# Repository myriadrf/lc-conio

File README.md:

# LibreCellular Remote Console and Power/Reset Control Boards

The CONIO boards provide remote console and power/reset control for SDR base
stations in the [LibreCellular CI hardware platform][1]. 

* **CONIO-A.** Controller (A) end.
* **CONIO-B.** Base station (B) end.

## Contents

The directory structure is as follows:

      /hardware/
          <board>/
              BOM/                   - Bill of materials
              Gerbers/               - Manufacturing files
              KiCAD/                 - KiCAD schematic and layout files
              Mechanical/            - STEP files
              PDF/                   - Schematic and layout PDFs

## Licence

LibreCellular CONIO is copyright 2021 AB Open Ltd and published under the
[Solderpad Hardware License v2.1][2]. 

[1]: https://librecellular.org/developer/ci_hardware.html
[2]: https://solderpad.org/licenses/SHL-2.1/

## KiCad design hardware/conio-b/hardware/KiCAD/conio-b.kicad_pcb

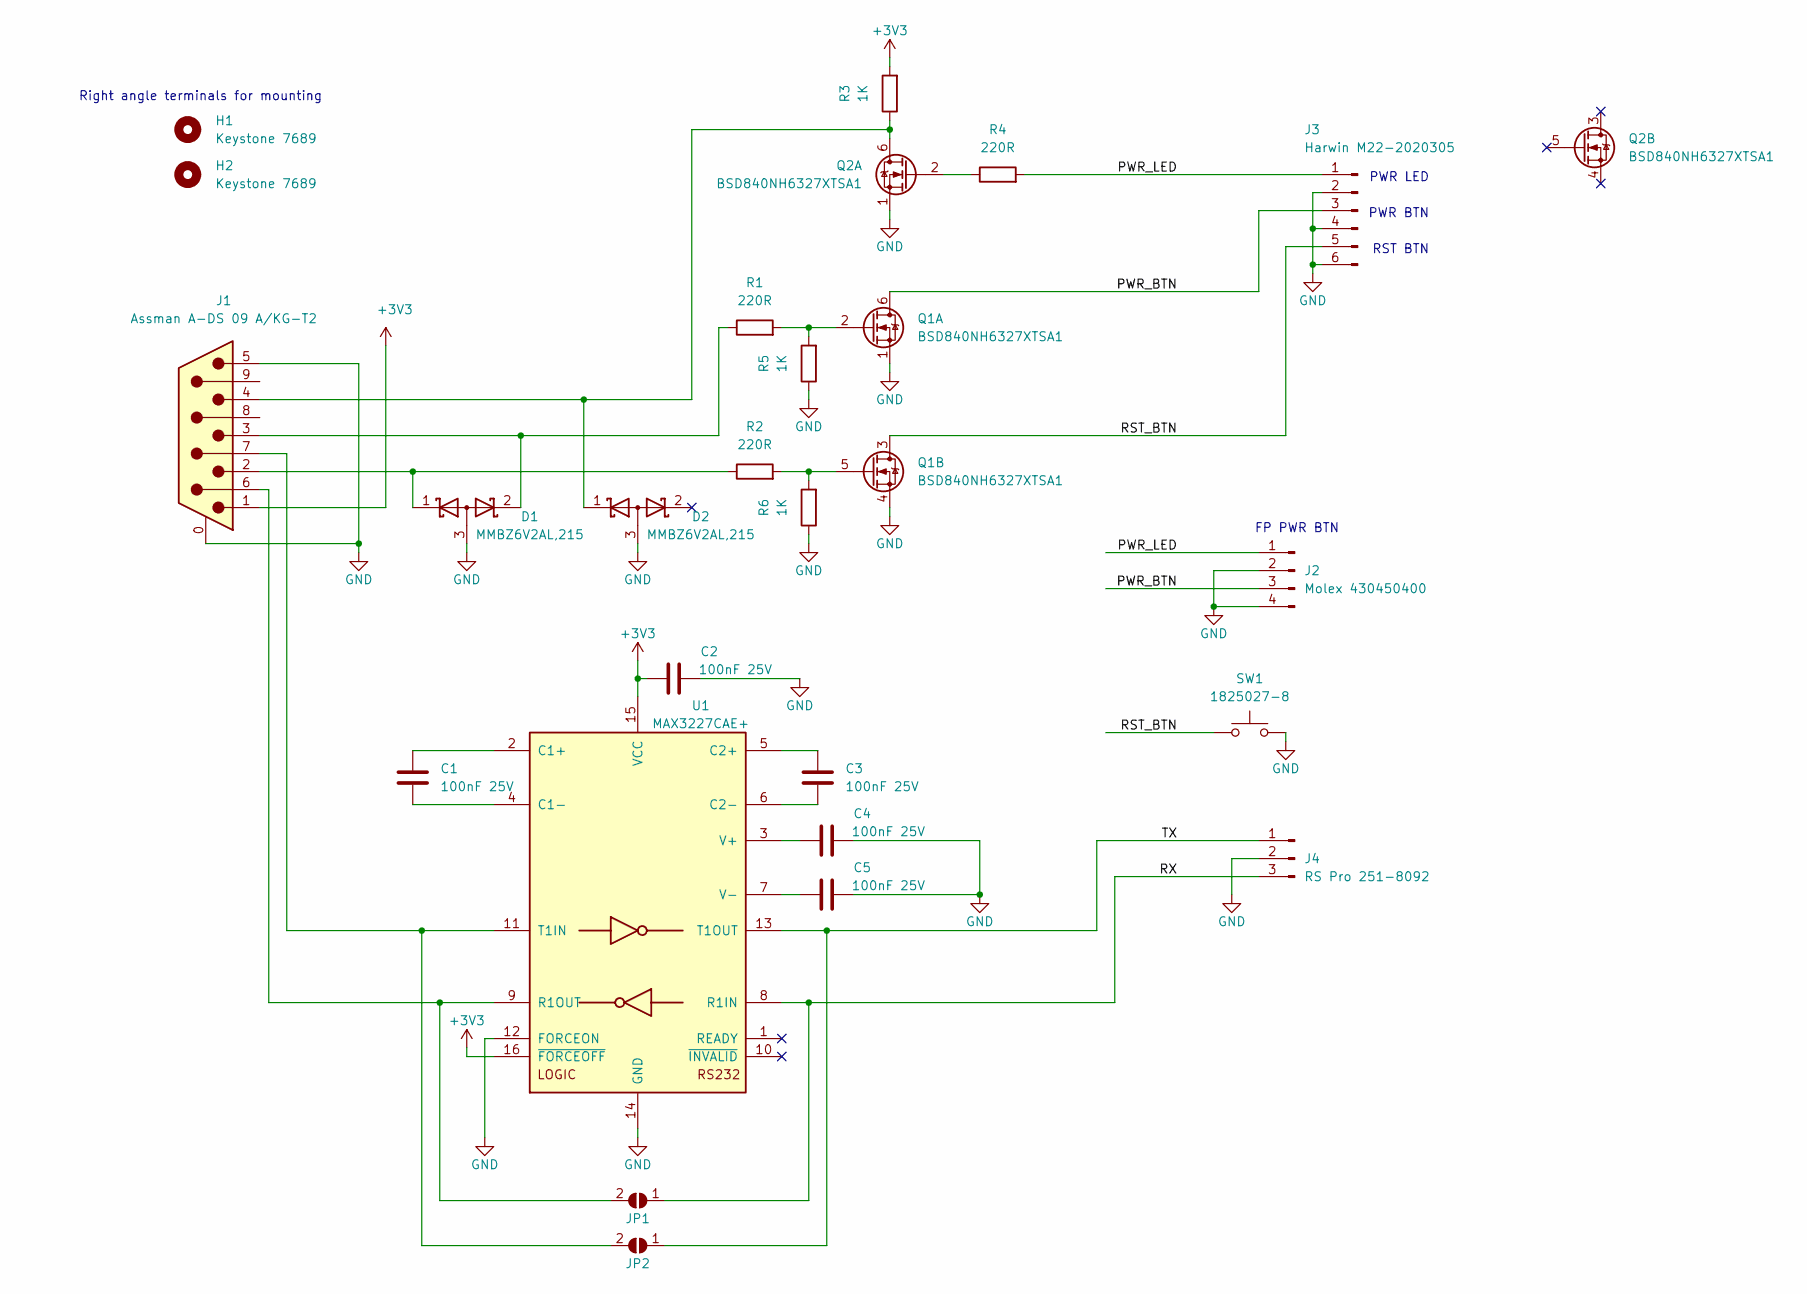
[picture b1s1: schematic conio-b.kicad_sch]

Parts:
C1, C2, C3, C4, C5: 100nF 25V; C_0603_1608Metric_Pad1.08x0.95mm_HandSolder; ManufacturerPN 06033C104KAZ2A
D1, D2: MMBZ6V2AL,215; SOT-23; ManufacturerPN MMBZ6V2AL,215
H1, H2: Keystone 7689; Keystone_7689_RA_PCB_Screw_Terminal; ManufacturerPN 7689
J1: Assman A-DS 09 A/KG-T2; Assman_A-DS_09_AKG-T2_Male_RA_TH_DB9; ManufacturerPN A-DS 09 A/KG-T2
J2: Molex 430450400; Molex_Micro-Fit_3.0_43045-0400_2x02_P3.00mm_Horizontal; ManufacturerPN 430450400
J3: Harwin M22-2020305; PinHeader_2x03_P2.00mm_Vertical; ManufacturerPN M22-2020305
J4: RS Pro 251-8092; PinSocket_1x03_P2.54mm_Vertical; ManufacturerPN 251-8092
JP1, JP2: SolderJumper_2_Open; SolderJumper-2_P1.3mm_Open_RoundedPad1.0x1.5mm
Q1, Q2: BSD840NH6327XTSA1; SOT-363_SC-70-6_Handsoldering; ManufacturerPN BSD840NH6327XTSA1
R1, R2, R4: 220R; R_0603_1608Metric_Pad0.98x0.95mm_HandSolder; ManufacturerPartNumber RC0603FR-07220RL
R3, R5, R6: 1K; R_0603_1608Metric_Pad0.98x0.95mm_HandSolder; ManufacturerPN RC0603FR-071KL
SW1: 1825027-8; TE_Connectivity_1825027-8_FSMRA3JH_Pushbutton; ManufacturerPN 1825027-8
U1: MAX3227CAE+; SSOP-16_5.3x6.2mm_P0.65mm; ManufacturerPN MAX3227CAE+

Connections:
+3V3: C2.1, J1.1, R3.2, U1.15 (VCC), U1.16 (~FORCEOFF)
/PWR_BTN: J2.3, J3.3, Q1.6 (D)
/PWR_LED: J2.1, J3.1, R4.2
/RST_BTN: J3.5, Q1.3 (D), SW1.1
/RX: J4.3, JP1.1 (A), U1.8 (R1IN)
/TX: J4.1, JP2.1 (A), U1.13 (T1OUT)
GND: C2.2, C4.2, C5.2, D1.3 (A), D2.3 (A), J1.0 (PAD), J1.5, J2.2, J2.4, J3.2, J3.4, J3.6, J4.2, Q1.1 (S), Q1.4 (S), Q2.1 (S), R5.1, R6.1, SW1.2, U1.12 (FORCEON), U1.14 (GND)
unnamed: C1.1, U1.2 (C1+)
unnamed: C1.2, U1.4 (C1-)
unnamed: C3.1, U1.5 (C2+)
unnamed: C3.2, U1.6 (C2-)
unnamed: C4.1, U1.3 (V+)
unnamed: C5.1, U1.7 (V-)
unnamed: D1.1 (K), J1.2, R2.1
unnamed: D1.2 (K), J1.3, R1.1
unnamed: D2.1 (K), J1.4, Q2.6 (D), R3.1
unnamed: J1.6, JP1.2 (B), U1.9 (R1OUT)
unnamed: J1.7, JP2.2 (B), U1.11 (T1IN)
unnamed: Q1.2 (G), R1.2, R5.2
unnamed: Q1.5 (G), R2.2, R6.2
unnamed: Q2.2 (G), R4.1
no_connect_24: D2.2 (K)
no_connect_25: Q2.3 (D)
no_connect_26: Q2.4 (S)
no_connect_27: Q2.5 (G)
no_connect_28: U1.1 (READY)
no_connect_29: U1.10 (~INVALID)

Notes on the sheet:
Right angle terminals for mounting
FP PWR BTN
PWR LED
PWR BTN
RST BTN

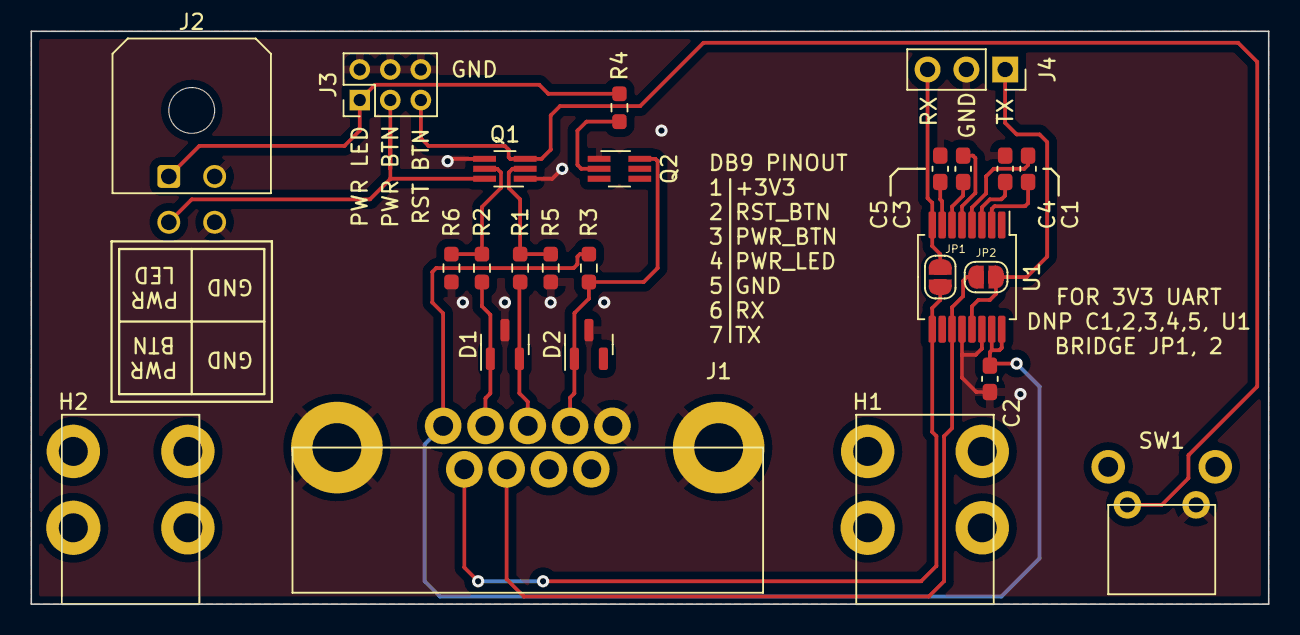
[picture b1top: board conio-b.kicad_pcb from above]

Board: 2 copper layers, 81.0 x 37.5 mm, 25 parts (0 on the bottom side), 21 nets.

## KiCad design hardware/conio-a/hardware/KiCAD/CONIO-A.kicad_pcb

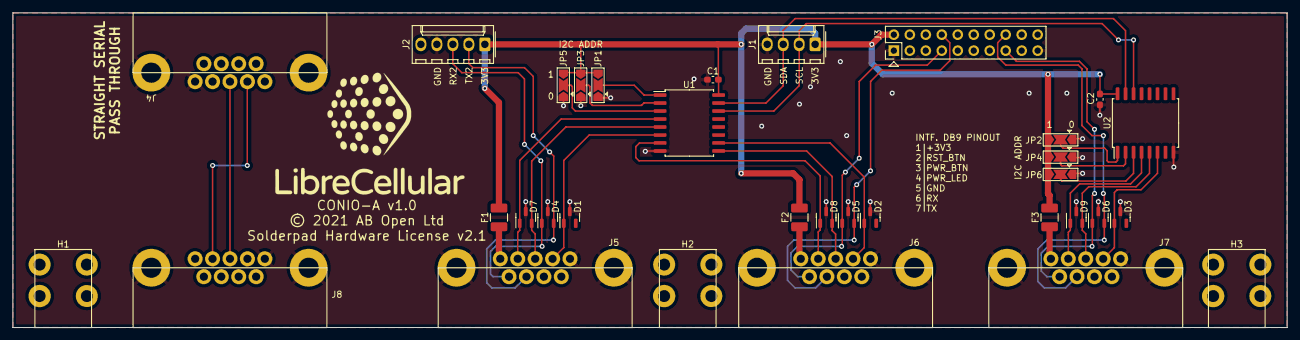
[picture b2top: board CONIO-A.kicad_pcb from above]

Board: 2 copper layers, 202.5 x 50.0 mm, 34 parts (0 on the bottom side), 30 nets.

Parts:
C1, C2: 100n 25V; C_0603_1608Metric_Pad1.08x0.95mm_HandSolder
D1, D2, D3, D4, D5, D6, D7, D8, D9: MMBZxx; SOT-23
F1, F2, F3: 0.05A; Fuse_1210_3225Metric_Pad1.42x2.65mm_HandSolder
H1, H2, H3: Keystone 7689; Keystone_7689_RA_PCB_Screw_Terminal
J1: Molex 22272041; Molex_KK-254_AE-6410-04A_1x04_P2.54mm_Vertical
J2: Molex 22272051; Molex_KK-254_AE-6410-05A_1x05_P2.54mm_Vertical
J3: Conn_02x10_Odd_Even; PinSocket_2x10_P2.54mm_Vertical_Flipped
J4, J5, J6, J7: DB9_Male_MountingHoles; Assman_A-DS_09_AKG-T2_Male_RA_TH_DB9
J8: DB9_Female_MountingHoles; Assman_A-DS_09_AKG-T2_Male_RA_TH_DB9
JP1, JP2, JP3, JP4, JP5, JP6: SolderJumper_3_Open; SolderJumper-3_P2.0mm_Open_TrianglePad1.0x1.5mm
Ref**: Val**; LibreCellular_Logo
U1, U2: PCF8574ADW; SOIC-16W_7.5x10.3mm_P1.27mm

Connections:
+3V3: C1.1, C2.1, F1.1, F2.1, F3.1, J1.1, J2.1, J3.2, JP1.3 (B), JP2.3 (B), JP3.3 (B), JP4.3 (B), JP5.3 (B), JP6.3 (B), U1.16 (VDD), U2.16 (VDD)
/PWR_BTN_2: D7.2 (K), J5.3, U1.5 (P1)
/PWR_BTN_3: D8.2 (K), J6.3, U1.9 (P4)
/PWR_BTN_4: D9.2 (K), J7.3, U2.5 (P1)
/PWR_LED_2: D1.1 (K), J5.4, U1.6 (P2)
/PWR_LED_3: D2.1 (K), J6.4, U1.10 (P5)
/PWR_LED_4: D3.1 (K), J7.4, U2.6 (P2)
/RST_BTN_2: D7.1 (K), J5.2, U1.4 (P0)
/RST_BTN_3: D8.1 (K), J6.2, U1.7 (P3)
/RST_BTN_4: D9.1 (K), J7.2, U2.4 (P0)
/RX2: D4.1 (K), J2.3, J5.6
/RX3: D5.1 (K), J3.7, J6.6
/RX4: D6.1 (K), J3.15, J7.6
/SCL: J1.2, U1.14 (SCL), U2.14 (SCL)
/SDA: J1.3, U1.15 (SDA), U2.15 (SDA)
/TX2: D4.2 (K), J2.2, J5.7
/TX3: D5.2 (K), J3.8, J6.7
/TX4: D6.2 (K), J3.16, J7.7
GND: C1.2, C2.2, D1.3 (A), D2.3 (A), D3.3 (A), D4.3 (A), D5.3 (A), D6.3 (A), D7.3 (A), D8.3 (A), D9.3 (A), J1.4, J2.4, J3.1, J3.19, J4.0 (PAD), J4.5, J5.0 (PAD), J5.5, J6.0 (PAD), J6.5, J7.0 (PAD), J7.5, J8.0 (PAD), J8.5, JP1.1 (A), JP2.1 (A), JP3.1 (A), JP4.1 (A), JP5.1 (A), JP6.1 (A), U1.8 (VSS), U2.8 (VSS)
unnamed: F1.2, J5.1
unnamed: F2.2, J6.1
unnamed: F3.2, J7.1
unnamed: J4.2, J8.2
unnamed: J4.3, J8.3
unnamed: JP1.2 (C), U1.1 (A0)
unnamed: JP2.2 (C), U2.1 (A0)
unnamed: JP3.2 (C), U1.2 (A1)
unnamed: JP4.2 (C), U2.2 (A1)
unnamed: JP5.2 (C), U1.3 (A2)
unnamed: JP6.2 (C), U2.3 (A2)

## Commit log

2021-08-13 Initial project commit
    - Added LICENSE file
    - Added CONIO-A and CONIO-B projects, organised into appropriate directory structure
2021-09-24 Minor reorg, add photo and update README.
2022-09-02 Remove duplicate licensing info

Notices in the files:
hardware/conio-a/hardware/KiCAD/CONIO-A.kicad_pcb:
© 2021 AB Open Ltd
